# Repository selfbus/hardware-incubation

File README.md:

# Deprecation Notice
Until May 11th 2023 selfbus hardware was split into "hardware" (stable projects) and "hardware-incubation" (dev projects). Since this split constantly lead to confusion mainly because stable hardware was not migrated to "hardware" but also because namings and structures differed between these two repositories, we decided to re-structe both to the same folder structure and merge them. In combination with clear collaboration rules it should be much easier now to understand what can be found where.

The newly created repository is located here: https://github.com/selfbus/hardware-merged

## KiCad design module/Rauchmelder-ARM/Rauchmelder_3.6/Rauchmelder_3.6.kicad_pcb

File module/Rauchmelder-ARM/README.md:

<h1>KNX interface for Gira Dual Q smoke detectors</h1>

This module is a well tested interface to get your Dual Q smoke detectors connected to your KNX bus. 

The unversioned Rauchmelder.sch and Rauchmelder.brd files are the development files. 
Once a new version is released, a corresponding copy of the files with the release version appended to the file name are provided. 

Project documentation: https://selfbus.org/wiki/devices/sensors/6-smoke-detector-module

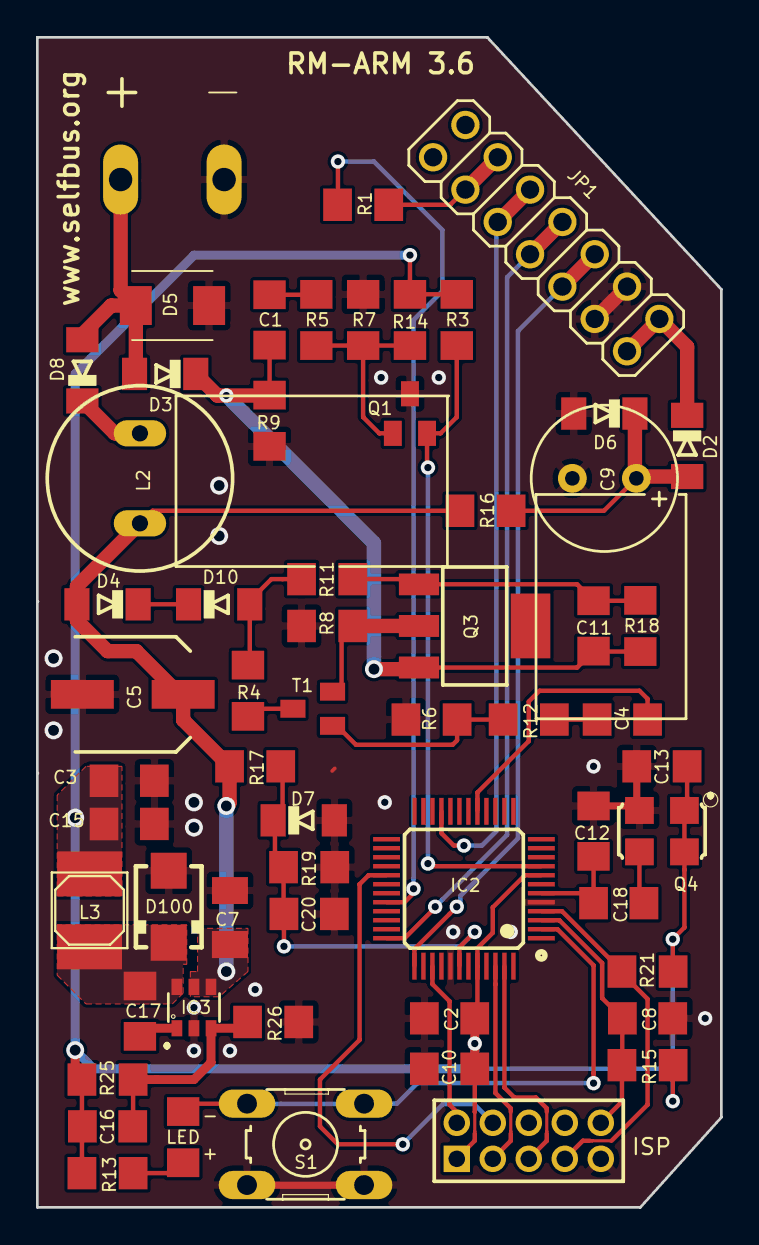
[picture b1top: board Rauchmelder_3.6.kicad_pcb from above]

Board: 2 copper layers, 38.0 x 65.0 mm, 59 parts (0 on the bottom side), 38 nets.

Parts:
C1, C3, C20: 100n; C1206
C2: 1µF; C1206
C4, C8, C11, C13: 10n; C1206
C5: 100µ; SANYO-OSCON_SMD_C6
C7: 4.7µF/50V; C1206K
C9: 330µ; E3,5-8
C10: 100nF; C1206
C12: 220p; C1206
C15: 22µ/10V; C1206
C16: 270n; C1206
C17: 15nF; C1206
C18: 100p; C1206
D2: BAT46; MINIMELF
D3, D4, D8: 1N4148; MINIMELF
D5: SMAJ40; SMBJ
D6: 12V; MINIMELF
D7: 3V6; MINIMELF
D10: 7,5V; MINIMELF
D100: MBRS1100; SMA
IC2: LPC1115; LQFP48
IC3: BD9G101; SOT23-6
JP1: PINHD-2X7; 2X07
JTAG1: J; 2X05M
L2: 150mH; BS11
L3: 6.8µH; PIS2812
LED1: LED3MM; R1206
Q1: BC856; SOT23-BEC
Q3: BCP52; SOT223
Q4: ASF
R1, R3, R5, R19: 10k; R1206
R4: 2k2; R1206
R6, R9, R15, R21: 100k; R1206
R7: 47k; R1206
R8: 5R6; R1206
R11, R13, R18: 1k; R1206
R12: 5k6; R1206
R14: 82k; R1206
R16: 22k; R1206
R17: 91k; R1206
R25: 2k4; R1206
R26: 680R; R1206
S1: 10-XX; B3F-10XX
T1: BC847C; SOT23
U$1: EIB; BUSKLEMME243-724

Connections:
+3V3: C2.2, C3.2, C10.2, C13.2, C15.2, C16.2, IC2.8, IC2.44, JTAG1.1, L3.P$2, Q4.1, Q4.4, R3.2, R13.1, R14.2, R15.1, R21.2, R25.2
/BUS_V1: C20.2, D7.C, IC2.42, R17.2, R19.1
/EIB_IN: IC2.9, Q1.E, R3.1
/EIB_OUT: C4.2, IC2.17
/IO14: IC2.47, JTAG1.5
/IO15: IC2.46, JTAG1.3
/ISP_EN: IC2.4, JTAG1.7, R21.1
/LT5: IC2.21, JP1.9, JP1.10
/LT8: IC2.32, R1.2
/PROG: IC2.2, LED1.1, S1.3, S1.4
/RESET: C8.2, IC2.3, JTAG1.10, R15.2
/RXD: IC2.37, JP1.5, JP1.6
/SWCLK: IC2.29, JTAG1.4
/SWDIO: IC2.39, JTAG1.2
/TXD: IC2.36, JP1.7, JP1.8
EIB_DC: C5.+, C7.2, D4.A, IC3.4, IC3.5, L2.2, R16.2, R17.1
GND: C2.1, C3.1, C5.-, C7.1, C8.1, C9.-, C10.1, C12.1, C13.1, C15.1, C20.1, D5.A, D6.A, D7.A, D100.A, IC2.5, IC2.41, IC3.2, JP1.3, JP1.4, JTAG1.9, Q1.C, Q4.2, R6.1, R7.1, R8.1, R9.1, R19.2, R26.1, S1.1, S1.2, U$1.1
unnamed: C1.1, C11.1, D3.C, Q3.3, R9.2, R18.2
unnamed: C1.2, R5.1
unnamed: C4.1, R12.1
unnamed: C9.+, D2.A, D6.C, R16.1
unnamed: C11.2, Q3.1, R11.1, R18.1
unnamed: C12.2, C18.2, IC2.6
unnamed: C16.1, IC3.3, R25.1, R26.2
unnamed: C17.1, D100.C, IC3.6, L3.P$1
unnamed: C17.2, IC3.1
unnamed: C18.1, Q4.3
unnamed: D2.C, JP1.1, JP1.2
unnamed: D3.A, D5.C, D8.A, U$1.2
unnamed: D8.C, L2.1
unnamed: D10.A, R4.2, R11.2
unnamed: D4.C, D10.C
unnamed: JP1.11, JP1.12, R1.1
unnamed: LED1.2, R13.2
unnamed: Q1.B, R5.2, R7.2, R14.1
unnamed: Q3.2, R8.2, T1.2
unnamed: R4.1, T1.3
unnamed: R6.2, R12.2, T1.1

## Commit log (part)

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2012-11-26 first upload
2013-01-06 first upload new version 4.3
2013-01-06 first upgrate to new basic circuit
2013-01-09 first upload SB_TS
2013-01-13 neue Versionen TS DIL zugefügt
2013-01-29 prototype Version, vorsicht änderung am osc
2013-01-30 Falsche Anmerkung entfernt
2013-02-10 Text entfernt/ geändert Signed-off-by: oldcoolman <service@krieger-elektro.de>
2013-02-19 first upload TS DIL
2013-02-21 RM2.0 first upload
2013-02-21 pinbelegung zugefügt
2013-02-21 Steckerbelegung um RXD und TXD erweitert Verzeichnis umbenannt auf "App-Controller Steckerbelegung"
2013-02-21 Verzeichnis umbenannt
2013-02-22 Pin Vext auf Versorgung korrigiert
2013-02-27 Alte Schaltungen entfernt
2013-03-01 Falsche Dateien entfernt, LED Taster besser benannt
2013-03-02 first revision Signed-off-by: oldcoolman <service@krieger-elektro.de>
2013-03-08 Umbauanleitung 1.3 auf 2.0
2013-03-15 add eagle files from raspberry pi controller version 1.0
2013-03-15 RPI Bus Controller: Prototyp entfernt, neue Version ins richtige Verzeichnis geschoben
2013-03-16 Creation of Eagle Libraries directory and add hammond boxes size
2013-03-25 Korrektur Verbindung 13->11, Dank an Tontechniker für die Meldung.
2013-03-28 CHG: CAP Package changed to 1206
2013-03-28 CHG wire angle fixed
2013-04-01 first upload Signed-off-by: oldcoolman <service@krieger-elektro.de>
2013-04-05 Taster Small Box V1
2013-04-06 SmallBox Change corrupt files
2013-04-06 New position for capacitor near to oscillator
2013-04-10 Rauchmelder Umbau auf Version 2.1
2013-05-07 upload usb progger
2013-05-11 Update der Rauchmelder Workarounds
2013-05-15 first upload usb modular
2013-05-19 first na du weisst schon...
2013-05-19 Dimmer V1.3 erstellt aus Dimmer V1 mit Workaround 3
2013-05-25 Gitignore for Eagle temp files, added missing C to dimmer workaround
2013-05-25 Updated the README and gitignore
2013-05-25 Torsteuerung initial upload
2013-05-25 Moved lpc922_4te to hardware repository, Renamed controller top-level directory to Controller, Moved 4te controller sub projects directly into Controller
2013-05-26 deleted
2013-06-07 Audioaktor: ICs beschriftet
2013-06-08 Rauchmelder verschoben nach hardware
2013-07-07 new 2TE Versions
2013-10-11 first upload oldi
2013-10-11 Tasterschnittstelle_DIL übersiedelte nach UPModule
2013-10-11 version 2.53 gelöscht und kerkobug 10nF am OSC von 1.54 gefixt.
2013-10-11 Zwischenversionen entfernt
2013-11-11 Regenmesser nach Apps verschoben.
2013-11-22 add a new version of top controller. the most part now one ONE side.
2013-12-14 modifiziert
2013-12-14 nochmal..
2014-01-17 Gira Tastsensor 3 CAD LibreCad
2014-01-21 aktualisierte .dxf des TS3
2014-01-21 aktualisierte DXF
2014-01-21 TS3 DXF Korrekturen
2014-02-03 2TE controller
2014-04-06 Entwurf ARM Controller 4TE
2014-04-06 Final V0.08
2014-04-06 Open questions added
2014-04-07 Exchange PWM and LT9
    To support a LPC11Uxx device and have the two pins required for the USB on
    the LED/Taster pinhead the old PWM and LT9 have been swaped.
2014-04-07 Additional GND added to App pinheader
    On pin 21 a new GND has been added. The following pins have been rearraged
    to keep all ADV channels.
2014-04-07 Improoved GND plane on BOT
2014-04-08 small changes
2014-04-08 C near Osci moved
2014-04-08 Beschriftungen aufgeräumt
    neue Datei: ARM-LPC1115_V0.10.brd
    neue Datei: ARM-LPC1115_V0.10.sch
2014-04-08 Small layout changes
2014-04-08 Version text on PCB changed
2014-05-17 duko gnd ergänzt, anschluss smcc
2014-05-24 LPC1115 SMD - Cleanup routing - Crystal and LEDs added
2014-05-25 LPC1115 SMD - 10nF X7R wie auf LPC Expressor Board hinzugefügt - Elko auf 3V3 Seite für Applikation mit erhöhtem Strombedarf hinzugefügt - 2 LEDs auf dem ARM Board hinzugefügt - Cleanup
2014-06-04 LPC1115 SMD: added GND VIAs
2014-06-04 LPC1115 SMD: Done! V1.0 RC 1 - TVS, Power Led hinzugefügt
2014-06-12 Labels angepasst, VSEL Pinhead update und umbenannt
2014-06-13 Bezeichungen verschoben und Hinweise ergänzt
2014-06-15 D2 bei Busspannungs-AD durch C ersetzt
2014-06-15 LPC1115 SMD: Low-Pass filter for ADC reading, silkscreen fixed
2014-06-15 ARM Controller Cleanup, ARM LCD+Taster
    - ARM Controller Verzeichnis aufgeräumt, letzte Version v1.0 genannt
    - ARM LCD+Taster Entwurf eingecheckt
2014-09-29 Added LPC compatibility pin information
2014-09-29 Update LPC compatibility pin information, LPC-Link cable added
2014-12-15 LPC922-DIL-SMD Adapter
2015-03-15 all components rearranged added programming interface with rm 2.54 (compatible with USB programmer) added TXD solder bridge preparation for horizontal WAGO
2015-04-28 New Version for RPi B+ and RPi 2B
2015-05-15 first upload TS-ARM3.05
2015-07-01 LPC-Link JP4
2015-10-07 current limiter for transmitter, change prog led behaviour, fix clamp layout
2015-11-20 fix receiver voltage protection
2015-12-21 umbau auf crystal, welches jedoch noch zu klein ist!
2016-01-12 HAT für FT12 einseitig bestückt
2016-01-16 TXD RXD getauscht
2016-01-17 Quarz footprint auf ASF geändert
2016-01-17 drc debug
2016-01-21 Schutzwiderstände in TXD_ARM und EIB-OUT_ARM eingefügt
2016-01-24 Beschriftung Ver/GND im Schaltplan berichtigt.
2016-01-25 Reduce VIAs, connect GND areas
2016-01-26 Fixed last commit
2016-02-07 Add TX/RX resistors and decoupling capacitors for ADUM.
2016-02-14 Raspi HAT Dual MCU - rerouted
2016-02-15 BUS-ADC zugefügt
2016-02-19 OSC mit C-teiler
2016-02-20 2TE controller mit OSC und C-Teiler
2016-02-22 VCC Leiche beim progtaster entfernt
2016-03-19 c Teiler beim OSC zugefügtV1.01
2016-03-19 LCD Taster PCB geroutet
2016-03-22 kosmetik
2016-03-29 Referenz vias zugefügt.
2016-03-31 stoplackflaeche im via pin3 OSC zugefuegt
2016-04-03 value cap divider changed, micro vias with tstop, and hole free on top
2016-04-03 cap dividor value changed
2016-04-04 Referenzvias zugefuegt.
2016-04-04 GND Vias, Silkscreen, etc. auf MCU Seite
2016-04-09 Finalize Raspi HAT Dual MCU board
2016-04-19 gnd via drill to 0.3mm, place separate bstop over this drills
2016-04-19 Kosmetik am 2TE ARM
2016-06-05 R Teiler für APP ID zugefügt
2016-06-12 Id-resistor package changed to 1206 and replace.
2016-06-12 Rauchmelder mit ARM 3.0
2016-06-12 Beschriftungen geändert
2016-10-20 pass via in cream mask deleted.
2016-10-23 runde cream entfernt
2016-12-11 IO / spi modify
2017-03-06 Added schematics and layouts for the 6x current-sensing switch module.
2017-04-14 Taster ARM erste Vorschlaege des Anschlusses am ARM.
2017-04-15 naechster Vorschlag
2017-04-16 vorschlag Erweiterungsstecker
2017-04-18 weiter geroutet...
2017-04-30 weiss nicht mehr...
2017-05-07 Paar Pauteile und vias verschoben
2017-05-09 Überwachung der Bodenplatte hinzugefügt + Beschriftung auf Platine verändert (Names layer)
    Die Überwachung, ob der Rauchmelder auf der Bodenplatte gesteckt und
    somit aktiv ist, wird über die interne Spannung des Rauchmelders
    erledigt. Diese ist an Pin 11+12 der Schnittstelle zu finden.
2017-07-21 WIP: Redesigning RM ARM PCB power supply and clock
2017-08-05 WIP: RM ARM routing done. Need to check ground VIAs and silk screen
2017-09-03 Update App out6_cs, update Controller lpc1115_4te_top
2017-09-03 Forgot to add the CAM project files...
2017-10-12 R29 auf out6_cs-ctrl V1.1 auf unbestückt geändert
2017-11-15 silkscreen tvalue not printing on brd
2018-03-22 DRC error beseitigt
2018-04-06 D100 insert with footprint sma
2018-04-08 aenderungen R12 C101, JP1
2018-04-08 overlap beseitigt
2018-04-09 Taster nach rechts geschoben
2018-04-11 Initial commit of RasPI-TPUART
2018-04-11 Revert "Initial commit of RasPI-TPUART"
    This reverts commit 3a7352cee3a7ec6d12a70a96cf5c11f9496d37f9.
2018-04-14 Add rx and tx led. Optional. Bridge the led pads, if no need.
2018-04-27 Unrouted error behoben
2018-07-16 Added Rauchmelder_3.6:
    - All parts are places on the top side (except for the long pin header,
    of course).
    - Gerber files for individual PCBs and for a 2-PCB panel with fiducials
    for pick-and-place.
    - Source files are in KiCAD-5.0 format
2018-07-16 Fix a few part values in Rauchmelder_3.5
2018-10-09 USB-Interface ARM hinzugefügt
2019-10-21 first official upload
2019-10-26 upload CNC data
2019-10-29 Connected PIN13 to ARM
    But see discussion here: https://selfbus.forums3.com/post4309.html#p4309
2020-01-09 KNX Steckklemmenblock initialer Upload
    3D-Druck Dateien zum Herstellen einer Halterung für Lötstifte, um mit einer KNX Steckklemme REG Geräte anzuschließen.
2020-03-15 2out_16A_bi_TS-ARM_V1.0 added
2020-03-15 neu: 2out-Gehäuse
2020-03-16 neu: Isoplatte für 2out-Gehäuse
2020-03-29 Spannungsteiler auf 91k/10k geändert
2021-02-16 V1.1 (ISP UART Header added)
2021-02-24 UART Header Label added
2021-05-02 Raincenter_APP_TS: first initial commit, KNX-module for the domestic waterworks ESPA-Tacomat or Raincenter Comfort 15
2021-05-02 New UP Module with fused IOs
    Initial commit of new in wall module with as many IOs as possible. New PCB size for solid walls and dry construction.
    Work in progress.
2021-09-07 Update of UP Module with fused IOs
    Completely changed how IOs will be protected. EEPROM and cropty IC added.
2021-11-05 UP Module with fused IOs: alpha version
    routing of a version with max. IOs / functions fitting on a single PCB for in-wall installation done. Parts size 0805.
2022-01-31 Schematic as PDF and Interactive BOM added.
2022-02-15 RPi-TPUART: Edited font sizes and tantalum markers
    Catching up on missing push from 2019.
2022-05-19 [LPC1115_4TE_TOP] added iBOM and eagle project
2022-05-19 [out6_cs] added iBOM and eagle project
2022-11-08 Anpassungen BOM out6_cs
2022-11-14 [2out_16A] added interactive BOM's
2022-11-30 [Raspi-TPUART] added interactive BOM
2023-01-22 [RM] - added buck enable voltage divider
    as discussed via chat the voltage divider values were set
    new parts for bus voltage detection added
2023-01-22 [RM] - optimized capacitors for ARM and routing
    2 x 1µF and 100nF were placed near ARM as well as 100pF in EIB_IN line to eliminate spikes
2023-01-22 [RM] - added second (optional) 22µF to optimize power supply
    --> ripple is further flattened
2023-01-22 [RM] - removed voltage divider again, added status LEDs, ...
    - after a long discussion: we should use nowhere the voltage divider!
    - status LEDs will help to identify problems when building the module
    - optimized schematic
    - added fiducials
    - changed D1 to SMA footprint again
2023-01-25 [RM] Addition of power supply switch
    The power supply has to be shut off before connecting the RM to the base plate. A few part are necessary to get this function on the board.
2023-01-25 [RM] Routed pwr suply switch / base detection
    Merged olterions change with most recent verison
    Routed addtional parts for base detection and pwr supply switch
    Removed accidentially added v3.8.3
2023-01-26 [RPi-HAT...] interactive BOM for v0.8, v0.9b, v0.9c
2023-01-26 [RM] - pwr mlccs changed to 2 x 47uF and adj-voltage divider 1k6/470R
    - according to ROHM spec: switched to 2 x 47uF mlccs (instead of 1 x 22uF of the old design)
    - according to ROHM spec: adjusted voltage divider to get 3,3V output instead of (instead of 3,397V from the old design)
2023-01-27 [RM] - removed thermals from buck converter polygons
2023-01-27 [RM] - changed footprints from 1206 to 0805
2023-01-28 [RM] - removed vendor attributes from parts
    attributes were not updated and thus were misleading because auf wrong c&p values. So it's better to delete them completely (and perhaps add a dedicated BOM later)
2023-01-29 [RM] - optimized silkscreen
2023-02-08 [RM] - changed values to standard values
2023-03-22 [RM] - rearranged diodes; added holes for pull out zip tie
2023-03-25 [RM] - corrected some small bugs
    corrected directions of status LEDs
    changed C102 1206 -> 0805
    changed L1 6.8uH -> 4.7uH
    changed C101 270 -> 470nF
2023-03-26 [RM] - corrected some small bugs - 2nd try
    something went wrong yesterday - now again:
    corrected directions of status LEDs
    changed C102 1206 -> 0805
    changed L1 6.8uH -> 4.7uH
    changed C101 270 -> 470nF
2023-04-19 [SB-TS] - deleted SB_TS (lpc922) board which was never finalised
2023-04-19 [TS-ARM] - new version TS ARM 3.09
